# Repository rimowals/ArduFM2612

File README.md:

# ArduFM2612

[Polski](#polski) | [English](#english)

---

## Polski

Syntezator FM na prawdziwym układzie **Yamaha YM2612 (OPN2)**, tym samym co w Sega Mega Drive / Genesis. Bez emulacji: dźwięk robi krzem, a ATmega328P (jak w Arduino Uno/Nano) tylko tłumaczy MIDI na rejestry YM-a. Nie ma też żadnej kompensacji „ladder effect”, więc brzmi tak brudno jak oryginał.

Projekt zaczął się na breadboardzie z Arduino Nano i płytką MIDI z Amigi CDTV, a skończył na własnej płytce. W repo jest wszystko, żeby go powtórzyć: schemat i PCB (KiCad 6), Gerbery i firmware.

Demo: https://www.youtube.com/watch?v=h-EnhL6LnMI

### Co potrafi

- 6 kanałów FM, domyślnie 6-głosowa polifonia, MIDI w trybie omni.
- Sterownik obsługuje też inne przydziały głosów (mono z 6 kanałami w unisonie, 3×2, 2×3, splity). Tryb ustawia się w kodzie przez `setPlaymode()`.
- 48 brzmień w formacie VGI zapisanych we flashu, przełączanych z MIDI.
- Każdy parametr każdego operatora ma swój CC, więc zwykły kontroler z gałkami (u mnie Korg nanoKONTROL) staje się edytorem FM na żywo.
- Pitch bend, LFO na mod wheelu.

### Sprzęt

- ATmega328P, 16 MHz, złącze ISP do programowania.
- Zegar dla YM2612 (8 MHz) generuje Timer1 ATmegi na pinie D9, bez osobnego oscylatora.
- Wejście MIDI izolowane transoptorem CNY17-1.
- Wyjście stereo: dwa LM386 (L/P) z trymerami głośności.
- Trzy stabilizatory: 7809 dla LM386 oraz osobne 7805 dla analogowej i cyfrowej części. Zasilacz musi dać na tyle dużo, żeby 7809 za diodą zabezpieczającą miał zapas (w praktyce ok. 12 V DC).

Schemat: `Doc/sch.PNG`, lista części: `Board/bom.txt`.

### Mapa CC

| CC | Funkcja |
|----|---------|
| 1 | LFO (mod wheel) |
| 14 | Feedback |
| 15 | AMS |
| 16 | FMS |
| 17 | Algorytm |
| 18 | Panorama (0, 1, 2) |
| 20–30 | Operator 1 |
| 40–50 | Operator 2 |
| 60–70 | Operator 3 |
| 80–90 | Operator 4 |
| 112 / 113 | Poprzednie / następne brzmienie |
| 117 | Reset układu |

Kolejność parametrów w każdym bloku operatora (od pierwszego CC): AR, DR, SR, RR, TL, SL, MUL, DT, RS, SSG-EG, AM. Czyli np. CC 41 to Decay Rate operatora 2.

### Jak zbudować

1. Zamów płytkę z plików w `Gerber/` (spakuj folder do ZIP i wyślij do JLCPCB, PCBWay itp.).
2. Wlutuj części według `Board/bom.txt`. Najpierw sprawdź zasilanie bez włożonych YM2612 i ATmegi.
3. Zainstaluj w Arduino IDE bibliotekę **MIDI Library** (FortySevenEffects), otwórz `Firmware/ARDU2612.ino` i wgraj na ATmega328P (przez ISP albo w Arduino, a potem przełóż kość). Jest też projekt dla Visual Studio + Visual Micro.
4. Podłącz klawiaturę MIDI i graj.

Retro chipy kupuję z kilku źródeł naraz i testuję wszystkie, bo jakość YM2612 z rynku wtórnego to loteria.

### Znane ograniczenia i co bym dziś zmienił

- Velocity jest na razie ignorowane.
- Nuty są transponowane o +36 w `handleNoteOn` – jeśli strój nie pasuje, zacznij od tego miejsca.
- Dałbym sprzętowy generator 8 MHz zamiast zegara z Timer1. YM miałby zegar także podczas resetu i wgrywania firmware'u, a zwolniony pin D9 pozwoliłby ułożyć szynę danych tak, żeby bity pokrywały się z portami (D0–D1 na PB0–PB1, D2–D7 na PD2–PD7). Wtedy zapis do YM-a to dwie instrukcje zamiast ośmiu `digitalWrite()`.

### Licencje

- Oprogramowanie: MIT (`LICENSE-SOFTWARE-MIT.txt`)
- Sprzęt: CERN-OHL-P-2.0 (`LICENSE-HARDWARE-CERN-OHL-P-2.0.txt`)

Możesz używać do czego chcesz, także komercyjnie, byle z zachowaniem informacji o licencji.

Sławomir (Slav) Cichoń

---

## English

An FM synth built around a real **Yamaha YM2612 (OPN2)**, the chip from the Sega Mega Drive / Genesis. No emulation: the silicon makes the sound, and an ATmega328P (same as in an Arduino Uno/Nano) just turns MIDI into YM register writes. There is no "ladder effect" compensation either, so it sounds as gritty as the original.

It started on a breadboard with an Arduino Nano and a MIDI board pulled out of an Amiga CDTV, and ended up on its own PCB. This repo has everything you need to build one: schematic and PCB (KiCad 6), Gerbers and firmware.

Demo: https://www.youtube.com/watch?v=h-EnhL6LnMI

### What it does

- 6 FM channels, 6-voice polyphony by default, MIDI in omni mode.
- The driver also supports other voice modes (6-channel unison mono, 3×2, 2×3, splits). Pick one in code with `setPlaymode()`.
- 48 patches in VGI format stored in flash, switchable over MIDI.
- Every parameter of every operator has its own CC, so any knob controller (I use a Korg nanoKONTROL) works as a live FM editor.
- Pitch bend, LFO on the mod wheel.

### Hardware

- ATmega328P at 16 MHz, ISP header for programming.
- The YM2612 clock (8 MHz) comes from the ATmega's Timer1 on pin D9, no separate oscillator.
- MIDI input isolated with a CNY17-1 optocoupler.
- Stereo output: two LM386 (L/R) with trim pots for level.
- Three regulators: a 7809 for the LM386s and separate 7805s for the analog and digital sides. The supply needs enough headroom for the 7809 after the protection diode (about 12 V DC in practice).

Schematic: `Doc/sch.PNG`, parts list: `Board/bom.txt`.

### CC map

| CC | Function |
|----|----------|
| 1 | LFO (mod wheel) |
| 14 | Feedback |
| 15 | AMS |
| 16 | FMS |
| 17 | Algorithm |
| 18 | Pan (0, 1, 2) |
| 20–30 | Operator 1 |
| 40–50 | Operator 2 |
| 60–70 | Operator 3 |
| 80–90 | Operator 4 |
| 112 / 113 | Previous / next patch |
| 117 | Chip reset |

Parameter order in each operator block (starting at its first CC): AR, DR, SR, RR, TL, SL, MUL, DT, RS, SSG-EG, AM. So CC 41 is operator 2 Decay Rate, for example.

### Building it

1. Order the PCB from the files in `Gerber/` (zip the folder and upload it to JLCPCB, PCBWay etc.).
2. Solder the parts from `Board/bom.txt`. Check the power rails before you put in the YM2612 and the ATmega.
3. Install **MIDI Library** (FortySevenEffects) in the Arduino IDE, open `Firmware/ARDU2612.ino` and flash it to the ATmega328P (via ISP, or in an Arduino and then move the chip). There is also a Visual Studio + Visual Micro project.
4. Plug in a MIDI keyboard and play.

I buy retro chips from several sellers at once and test all of them. Second-hand YM2612s are a lottery.

### Known limitations and what I'd change today

- Velocity is ignored for now.
- Notes are transposed by +36 in `handleNoteOn`. If the tuning is off, start there.
- I'd use a hardware 8 MHz oscillator instead of the Timer1 clock. The YM would keep its clock during reset and flashing, and the freed D9 pin would let the data bus line up with the ports (D0–D1 on PB0–PB1, D2–D7 on PD2–PD7), so a register write takes two port writes instead of eight `digitalWrite()` calls.

### Licenses

- Software: MIT (`LICENSE-SOFTWARE-MIT.txt`)
- Hardware: CERN-OHL-P-2.0 (`LICENSE-HARDWARE-CERN-OHL-P-2.0.txt`)

Use it for anything you like, commercial use included, as long as you keep the license notices.

Sławomir (Slav) Cichoń

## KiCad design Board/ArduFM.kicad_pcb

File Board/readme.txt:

Board (KiCad)
=============

Zawartość
---------
- ArduFM.kicad_pro -> projekt główny
- ArduFM.kicad_sch -> schemat
- ArduFM.kicad_pcb -> PCB
- bom.txt          -> lista elementów

Wskazówki montażowe
-------------------
- Zacznij od elementów niskich (rezystory, diody), potem podstawki/układy,
  na końcu elektrolity i złącza.
- Sprawdź orientację:
  - diody (1N4004, 1N4148),
  - LED,
  - elektrolity,
  - układy DIP (pin 1),
  - stabilizatory 78xx.
- Po montażu wykonaj testy sekcji zasilania bez włożonych drogich układów.

BOM
---
Oficjalna lista części znajduje się w pliku bom.txt.

Produkcja PCB
-------------
Do zamówienia płytek użyj folderu Gerber/ z katalogu głównego repo.

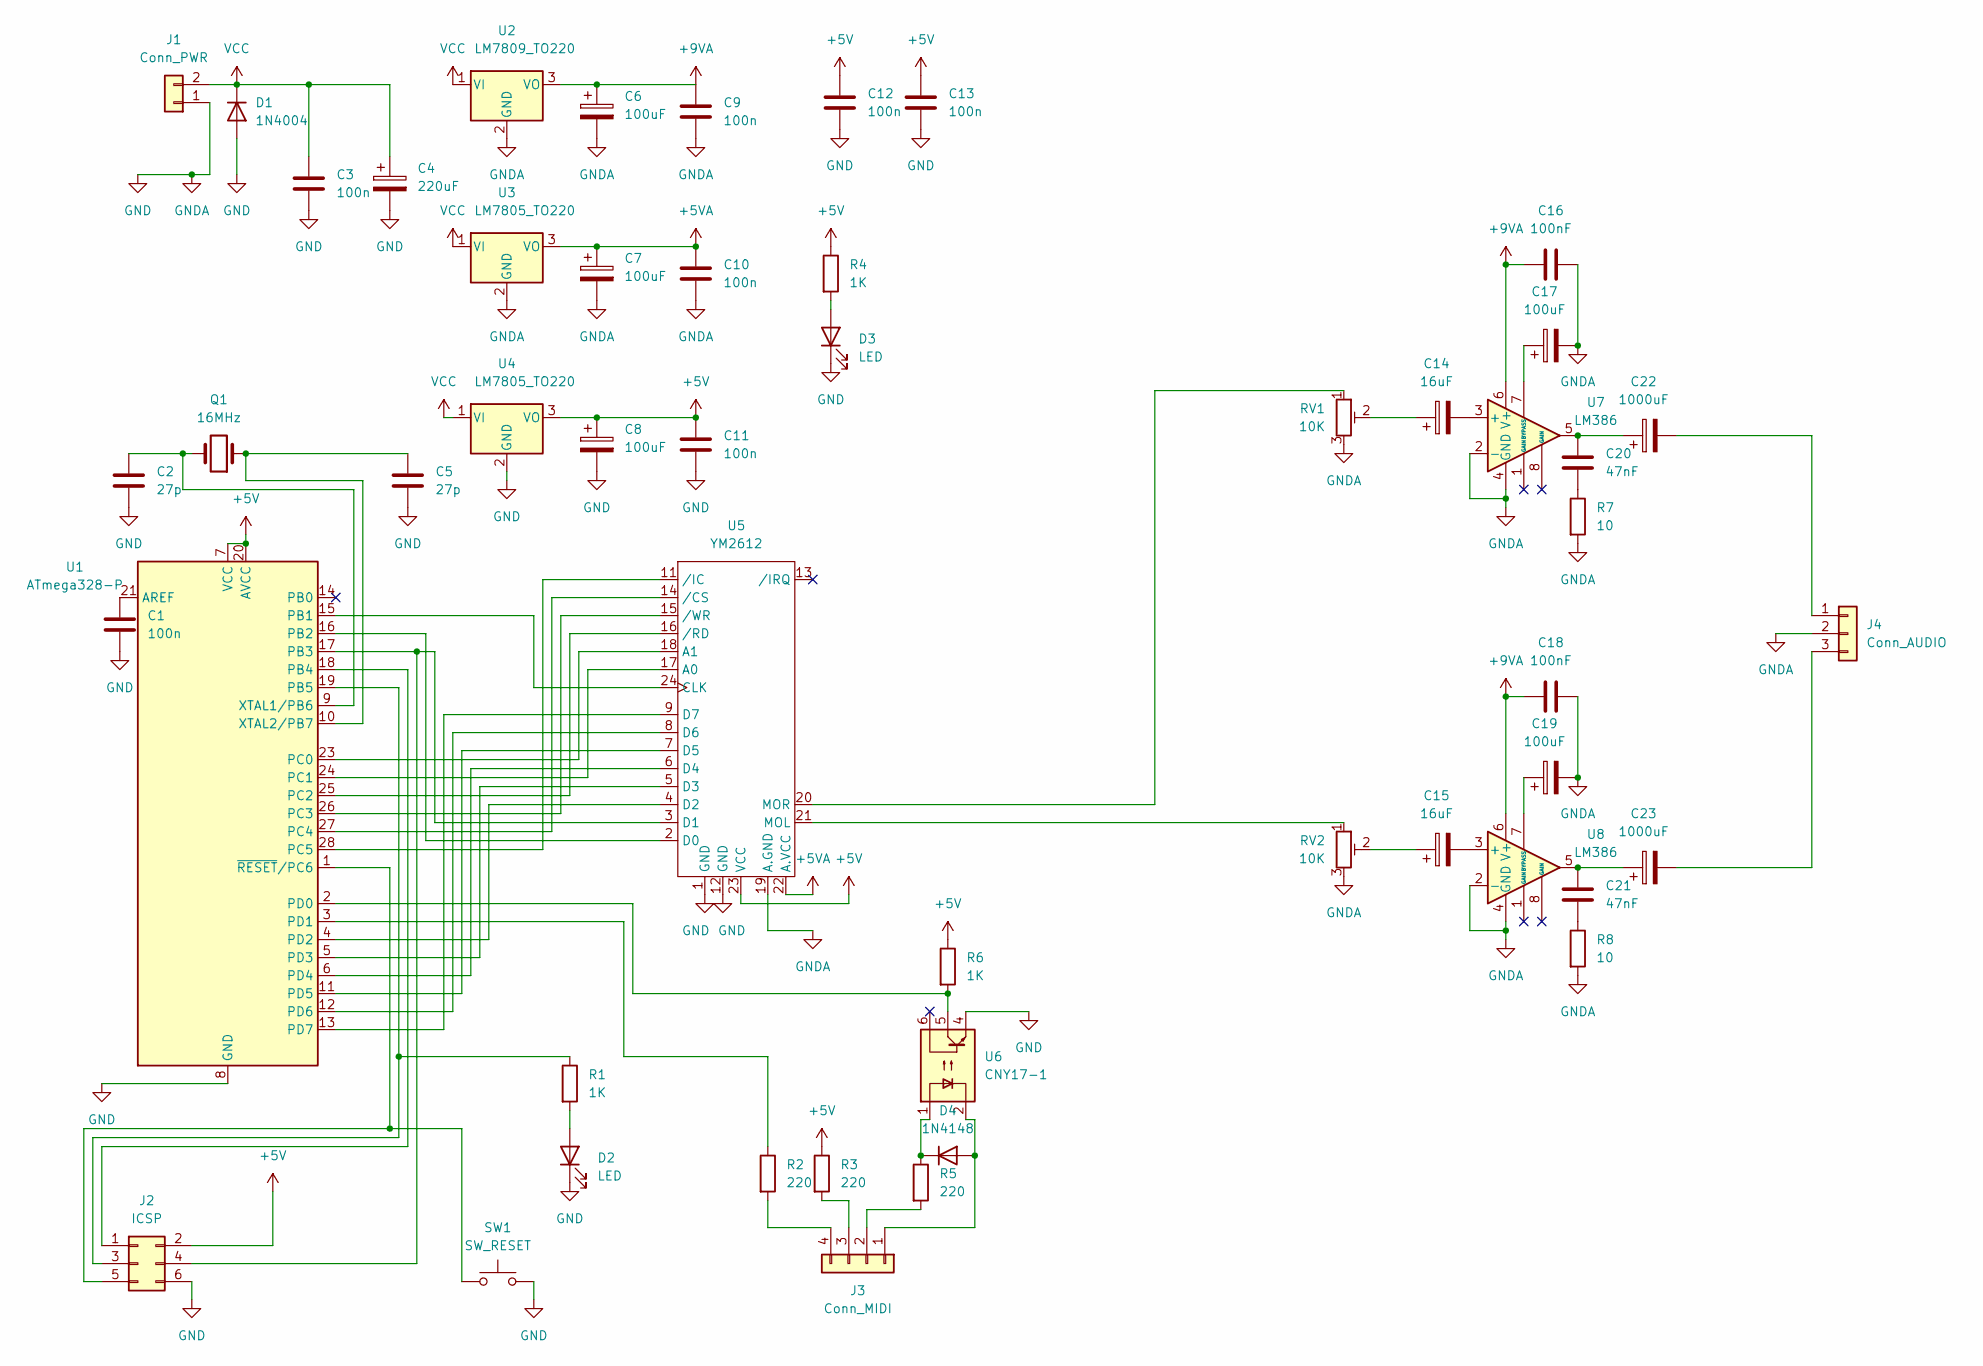
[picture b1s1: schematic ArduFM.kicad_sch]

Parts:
C1, C3, C9, C10, C11, C12, C13: 100n; C_Rect_L7.0mm_W2.5mm_P5.00mm
C2, C5: 27p; C_Disc_D5.0mm_W2.5mm_P5.00mm
C4: 220uF; CP_Radial_D7.5mm_P2.50mm
C6, C7, C8, C17, C19: 100uF; CP_Radial_D6.3mm_P2.50mm
C14, C15: 16uF; CP_Radial_D5.0mm_P2.00mm
C16, C18: 100nF; C_Rect_L7.0mm_W2.5mm_P5.00mm
C20, C21: 47nF; C_Rect_L7.0mm_W2.5mm_P5.00mm
C22, C23: 1000uF; CP_Radial_D10.0mm_P5.00mm
D1: 1N4004; D_DO-41_SOD81_P10.16mm_Horizontal
D2, D3: LED; LED_D3.0mm_FlatTop
D4: 1N4148; D_DO-35_SOD27_P7.62mm_Horizontal
J1: Conn_PWR; PinHeader_1x02_P2.54mm_Vertical
J2: ICSP; PinHeader_2x03_P2.54mm_Vertical
J3: Conn_MIDI; PinHeader_1x04_P2.54mm_Vertical
J4: Conn_AUDIO; PinHeader_1x03_P2.54mm_Vertical
Q1: 16MHz; Crystal_HC49-4H_Vertical
R1, R4, R6: 1K; R_Axial_DIN0207_L6.3mm_D2.5mm_P10.16mm_Horizontal
R2, R3, R5: 220; R_Axial_DIN0207_L6.3mm_D2.5mm_P10.16mm_Horizontal
R7, R8: 10; R_Axial_DIN0207_L6.3mm_D2.5mm_P10.16mm_Horizontal
RV1, RV2: 10K; Potentiometer_ACP_CA9-H2,5_Horizontal
SW1: SW_RESET; SW_Tactile_Straight_KSL0Axx1LFTR
U1: ATmega328-P; DIP-28_W7.62mm
U2: LM7809_TO220; TO-220-3_Vertical
U3, U4: LM7805_TO220; TO-220-3_Vertical
U5: YM2612; DIP-24_W15.24mm_LongPads
U6: CNY17-1; DIP-6_W7.62mm_LongPads
U7, U8: LM386; DIP-8_W7.62mm

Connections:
+5V: C8.1, C11.1, C12.1, C13.1, J2.2, R3.1, R4.1, R6.1, U1.7 (VCC), U1.20 (AVCC), U4.3 (VO), U5.23 (VCC)
+5VA: C7.1, C10.1, U3.3 (VO), U5.22 (A.VCC)
+9VA: C6.1, C9.1, C16.1, C18.1, U2.3 (VO), U7.6 (V+), U8.6 (V+)
GND: C1.2, C2.2, C3.2, C4.2, C5.2, C6.2, C7.2, C8.2, C9.2, C10.2, C11.2, C12.2, C13.2, C16.2, C17.2, C18.2, C19.2, D1.2 (A), D2.1 (K), D3.1 (K), J1.1, J2.6, J4.2, R7.2, R8.2, RV1.3, RV2.3, SW1.2, U1.8 (GND), U1.22 (GND), U2.2 (GND), U3.2 (GND), U4.2 (GND), U5.1 (GND), U5.12 (GND), U5.19 (A.GND), U6.4, U7.2 (-), U7.4 (GND), U8.2 (-), U8.4 (GND)
unnamed: C1.1, U1.21 (AREF)
unnamed: C2.1, Q1.2, U1.9 (XTAL1/PB6)
unnamed: C5.1, Q1.1, U1.10 (XTAL2/PB7)
unnamed: C14.1, RV1.2
unnamed: C14.2, U7.3 (+)
unnamed: C15.1, RV2.2
unnamed: C15.2, U8.3 (+)
unnamed: C17.1, U7.7 (BYPASS)
unnamed: C19.1, U8.7 (BYPASS)
unnamed: C20.1, C22.1, U7.5
unnamed: C20.2, R7.1
unnamed: C21.1, C23.1, U8.5
unnamed: C21.2, R8.1
unnamed: C22.2, J4.1
unnamed: C23.2, J4.3
unnamed: D2.2 (A), R1.2
unnamed: D3.2 (A), R4.2
unnamed: D4.1 (K), R5.1, U6.1
unnamed: D4.2 (A), J3.1, U6.2
unnamed: J3.2, R5.2
unnamed: J3.3, R3.2
unnamed: J3.4, R2.2
unnamed: J2.3, R1.1, U1.19 (PB5)
unnamed: R2.1, U1.3 (PD1)
unnamed: R6.2, U1.2 (PD0), U6.5
unnamed: RV1.1, U5.20 (MOR)
unnamed: RV2.1, U5.21 (MOL)
unnamed: J2.5, SW1.1, U1.1 (~RESET/PC6)
unnamed: U1.4 (PD2), U5.4 (D2)
unnamed: U1.5 (PD3), U5.5 (D3)
unnamed: U1.6 (PD4), U5.6 (D4)
unnamed: U1.11 (PD5), U5.7 (D5)
unnamed: U1.12 (PD6), U5.8 (D6)
unnamed: U1.13 (PD7), U5.9 (D7)
unnamed: U1.15 (PB1), U5.24 (CLK)
unnamed: U1.16 (PB2), U5.2 (D0)
unnamed: J2.4, U1.17 (PB3), U5.3 (D1)
unnamed: J2.1, U1.18 (PB4)
unnamed: U1.23 (PC0), U5.18 (A1)
unnamed: U1.24 (PC1), U5.17 (A0)
unnamed: U1.25 (PC2), U5.16 (/RD)
unnamed: U1.26 (PC3), U5.15 (/WR)
unnamed: U1.27 (PC4), U5.14 (/CS)
unnamed: U1.28 (PC5), U5.11 (/IC)
VCC: C3.1, C4.1, D1.1 (K), J1.2, U2.1 (VI), U3.1 (VI), U4.1 (VI)

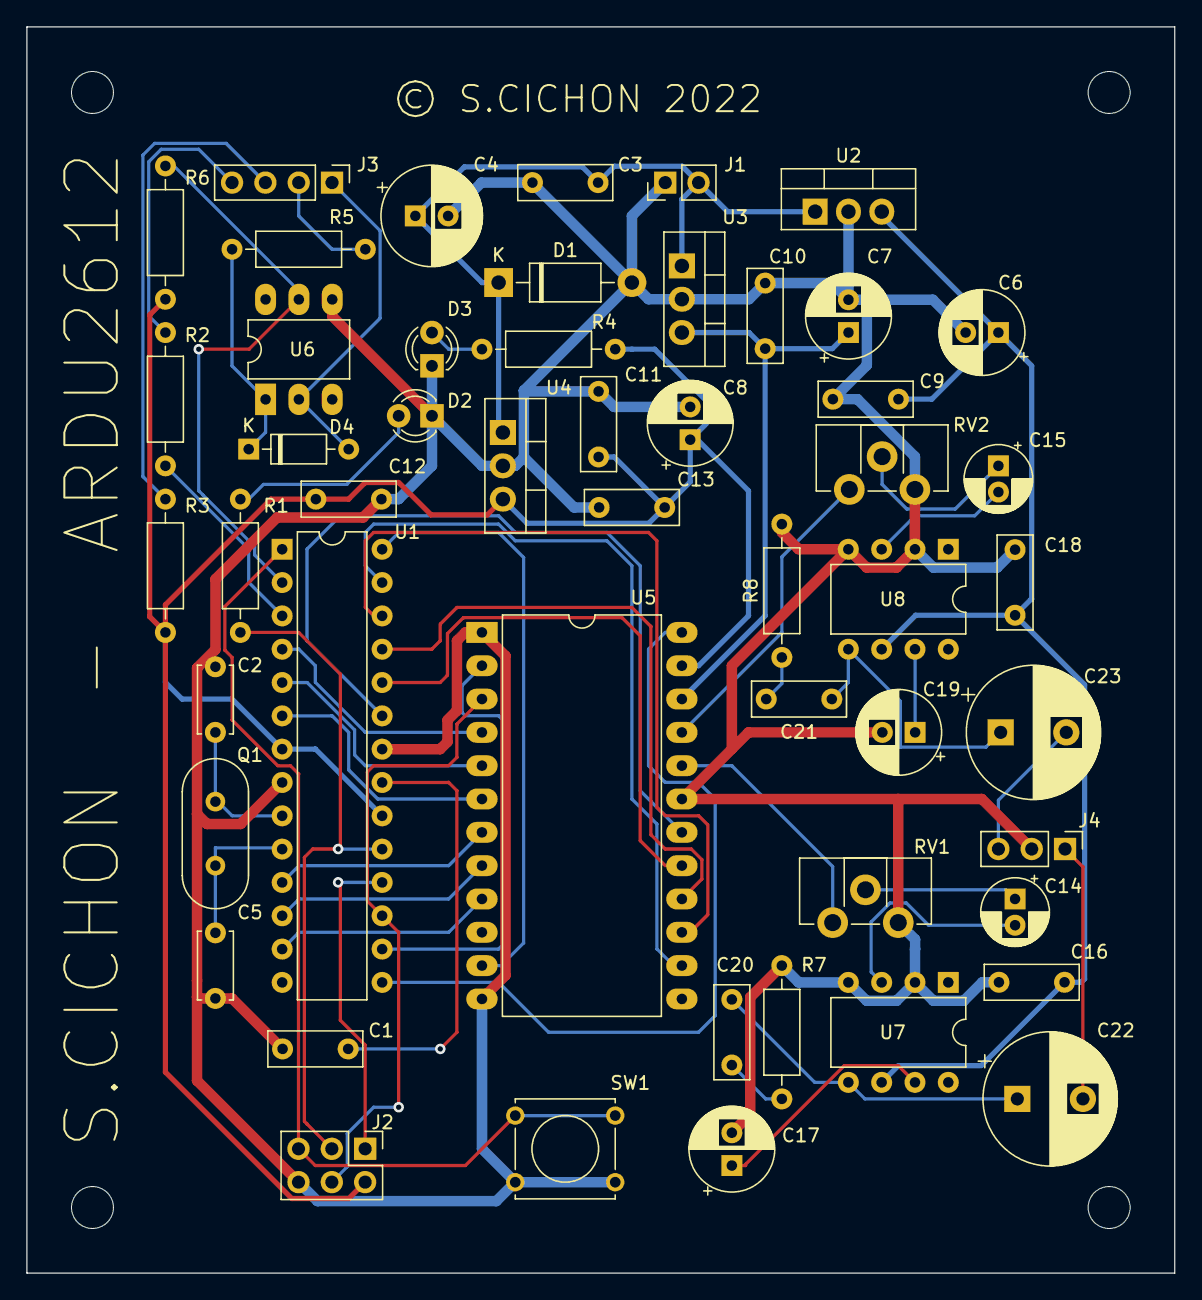
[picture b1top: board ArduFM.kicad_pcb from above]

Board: 2 copper layers, 87.5 x 95.0 mm, 51 parts (0 on the bottom side), 49 nets.

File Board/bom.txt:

"Reference","Value","Datasheet","Footprint","Qty","DNP"
"C1,C3,C9,C10,C11,C12,C13","100n","~","Capacitor_THT:C_Rect_L7.0mm_W2.5mm_P5.00mm","7",""
"C2,C5","27p","~","Capacitor_THT:C_Disc_D5.0mm_W2.5mm_P5.00mm","2",""
"C4","220uF","~","Capacitor_THT:CP_Radial_D7.5mm_P2.50mm","1",""
"C6,C7,C8,C17,C19","100uF","~","Capacitor_THT:CP_Radial_D6.3mm_P2.50mm","5",""
"C14,C15","16uF","~","Capacitor_THT:CP_Radial_D5.0mm_P2.00mm","2",""
"C16,C18","100nF","~","Capacitor_THT:C_Rect_L7.0mm_W2.5mm_P5.00mm","2",""
"C20,C21","47nF","~","Capacitor_THT:C_Rect_L7.0mm_W2.5mm_P5.00mm","2",""
"C22,C23","1000uF","~","Capacitor_THT:CP_Radial_D10.0mm_P5.00mm","2",""
"D1","1N4004","http://www.vishay.com/docs/88503/1n4001.pdf","Diode_THT:D_DO-41_SOD81_P10.16mm_Horizontal","1",""
"D2,D3","LED","~","LED_THT:LED_D3.0mm_FlatTop","2",""
"D4","1N4148","https://assets.nexperia.com/documents/data-sheet/1N4148_1N4448.pdf","Diode_THT:D_DO-35_SOD27_P7.62mm_Horizontal","1",""
"J1","Conn_PWR","~","Connector_PinHeader_2.54mm:PinHeader_1x02_P2.54mm_Vertical","1",""
"J2","ICSP","~","Connector_PinHeader_2.54mm:PinHeader_2x03_P2.54mm_Vertical","1",""
"J3","Conn_MIDI","~","Connector_PinHeader_2.54mm:PinHeader_1x04_P2.54mm_Vertical","1",""
"J4","Conn_AUDIO","~","Connector_PinHeader_2.54mm:PinHeader_1x03_P2.54mm_Vertical","1",""
"Q1","16MHz","~","Crystal:Crystal_HC49-4H_Vertical","1",""
"R1,R4,R6","1K","~","Resistor_THT:R_Axial_DIN0207_L6.3mm_D2.5mm_P10.16mm_Horizontal","3",""
"R2,R3,R5","220","~","Resistor_THT:R_Axial_DIN0207_L6.3mm_D2.5mm_P10.16mm_Horizontal","3",""
"R7,R8","10","~","Resistor_THT:R_Axial_DIN0207_L6.3mm_D2.5mm_P10.16mm_Horizontal","2",""
"RV1,RV2","10K","~","Potentiometer_THT:Potentiometer_ACP_CA9-H2,5_Horizontal","2",""
"SW1","SW_RESET","~","Button_Switch_THT:SW_Tactile_Straight_KSL0Axx1LFTR","1",""
"U1","ATmega328-P","http://ww1.microchip.com/downloads/en/DeviceDoc/ATmega328_P%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","Package_DIP:DIP-28_W7.62mm","1",""
"U2","LM7809_TO220","https://www.onsemi.cn/PowerSolutions/document/MC7800-D.PDF","Package_TO_SOT_THT:TO-220-3_Vertical","1",""
"U3,U4","LM7805_TO220","https://www.onsemi.cn/PowerSolutions/document/MC7800-D.PDF","Package_TO_SOT_THT:TO-220-3_Vertical","2",""
"U5","YM2612","","Package_DIP:DIP-24_W15.24mm_LongPads","1",""
"U6","CNY17-1","http://www.vishay.com/docs/83606/cny17.pdf","Package_DIP:DIP-6_W7.62mm_LongPads","1",""
"U7,U8","LM386","http://www.ti.com/lit/ds/symlink/lm386.pdf","Package_DIP:DIP-8_W7.62mm","2",""

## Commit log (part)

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2026-02-05 First publication

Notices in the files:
Board/ArduFM.kicad_pcb:
© S.CICHON 2022
